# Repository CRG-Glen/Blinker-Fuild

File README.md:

# BLINKER FLUID

A completely pointless project.  

## What's this?  

Intended to sit inline with your 68000 CPU with LEDs on each signal that will light when that signal becomes active. 

It's just for fun and should not to be used for any diagnostic purposes, this isn't a logic probe!

There are 8nr 74HCT574s which are sampling each pin on the rising edge of a clock generated by a 555 timer.  
The 555 is running at a rate of approximately 50hz so will miss a lot of activity on the 68k.  There just
isn't enough room to do this with any accuracy but remember this is for fun only.  

You can adjust R71 and R72 to change the speed of the 555. 

## Assembly

Within the JLCPCB folder you will find Gerbers along with a BOM and CPL files suited to LCSC components.

The board can be produced with the HASL finish, no need to pay for EINT on this one but its mostly 0603 so 
get JLC (or equal) to do all SMD work.

Please note the BOM as included takes for RED LEDs for everything.  Feel free to change colours but remember 
you also need to adjust the resistor directly below each LED on the bottom side to suit your LEDs!

To keep the board tidy, there are no LED or Resistor designations on the PCB.  Just remember its all LEDs 
on the top side and all RESISTORs on the bottom side.  

## Bill of Materials

| Designation | Value | Type |
| --- | --- | --- |
| U1 - U8 | 74HCT574 | TSSOP20 |
| U9 | NE555 | TSSOP8 |
| LEDs | pick a colour | 0603 |
| Resistors | to suit your LED | 0603 |
| R71 | 1k ohm 1% | 0805 |
| R72 | 15kohm 1% | 0805 |
| C71 | 1uF | 0805 Tantalum |
| C72 | 10nF |0805 ceramic |
| C1-C8 + C73 | 0.1uF | 0603 ceramic |
| PINS | 0.5mm x 2.54mm x 9.7mm | individual machine pins |

## License

CERN Open Hardware Licence v2

Do with as you like just don't blame me if your computer, console or whatever else you install this in
goes up in smoke!

## Credits

PCB by CRG(Glen)

Artwork by Brick Studios

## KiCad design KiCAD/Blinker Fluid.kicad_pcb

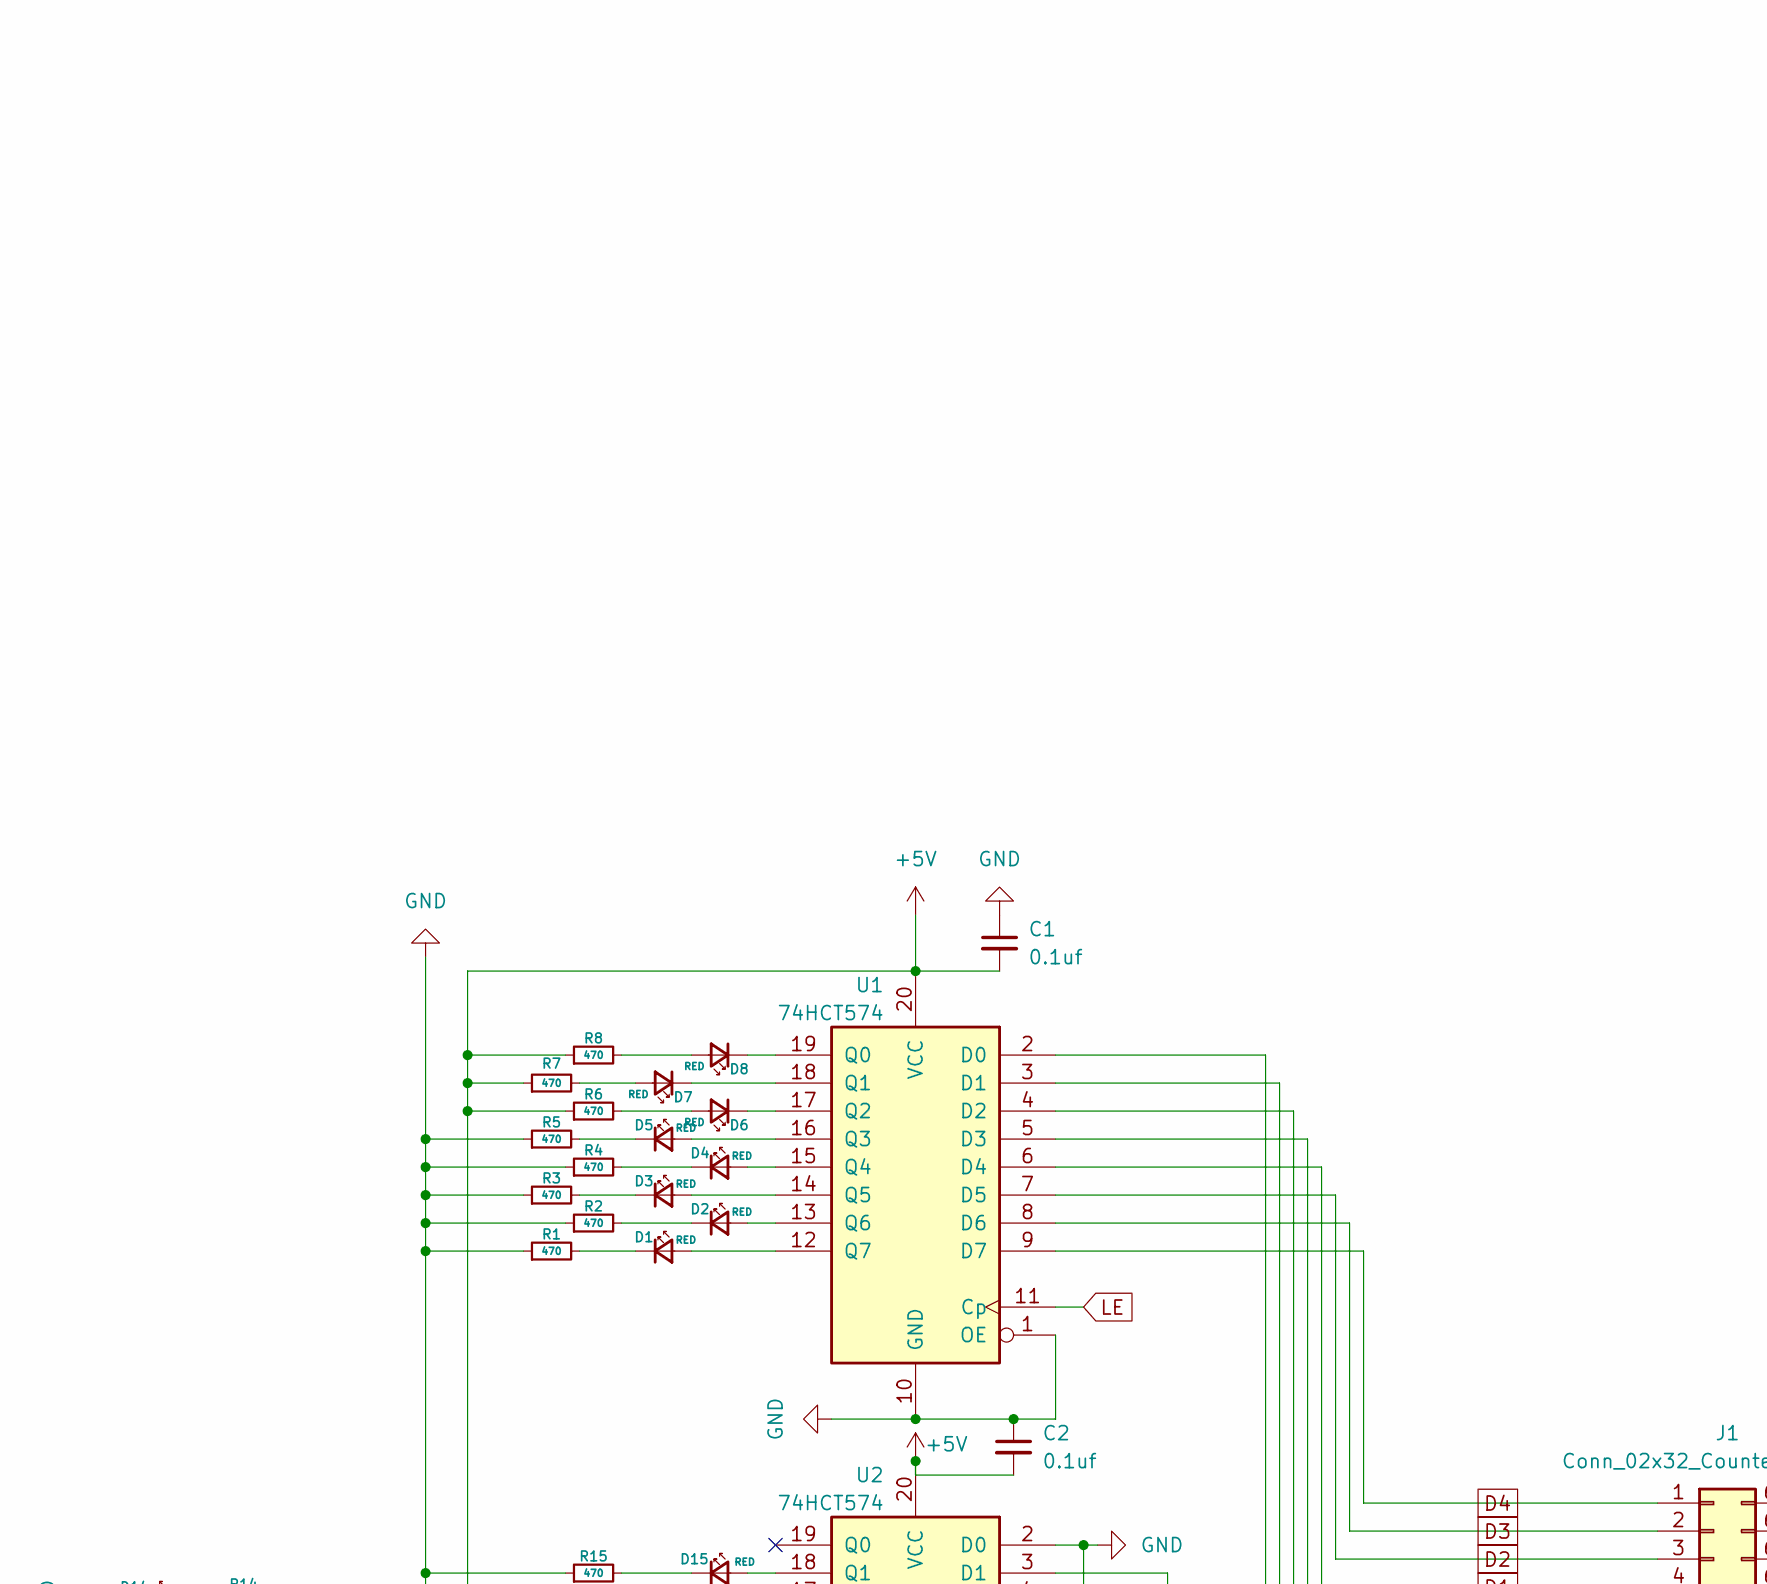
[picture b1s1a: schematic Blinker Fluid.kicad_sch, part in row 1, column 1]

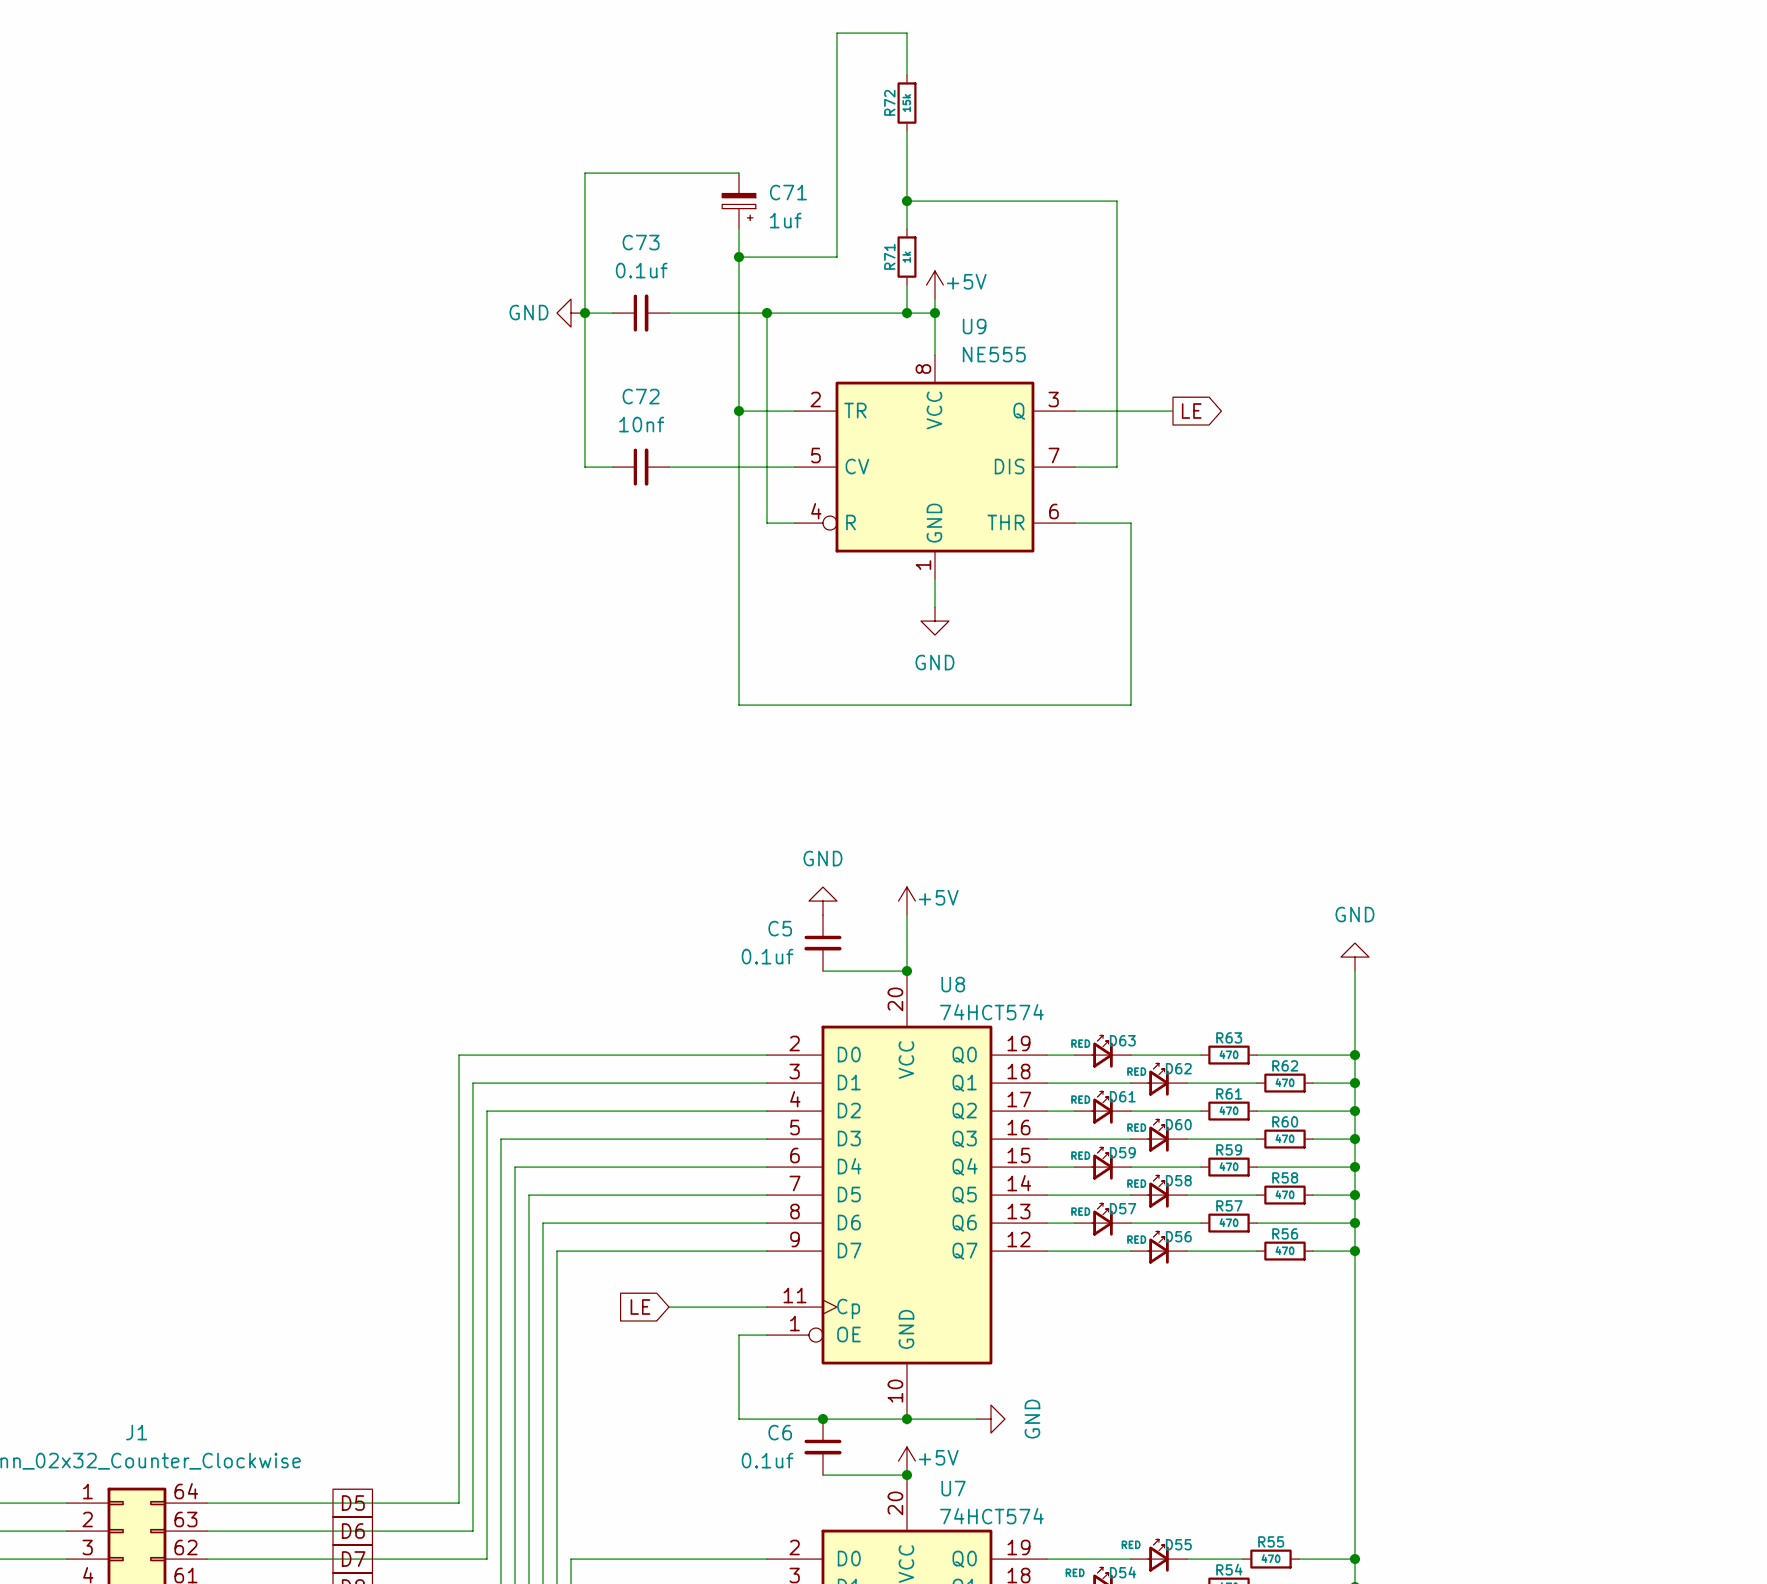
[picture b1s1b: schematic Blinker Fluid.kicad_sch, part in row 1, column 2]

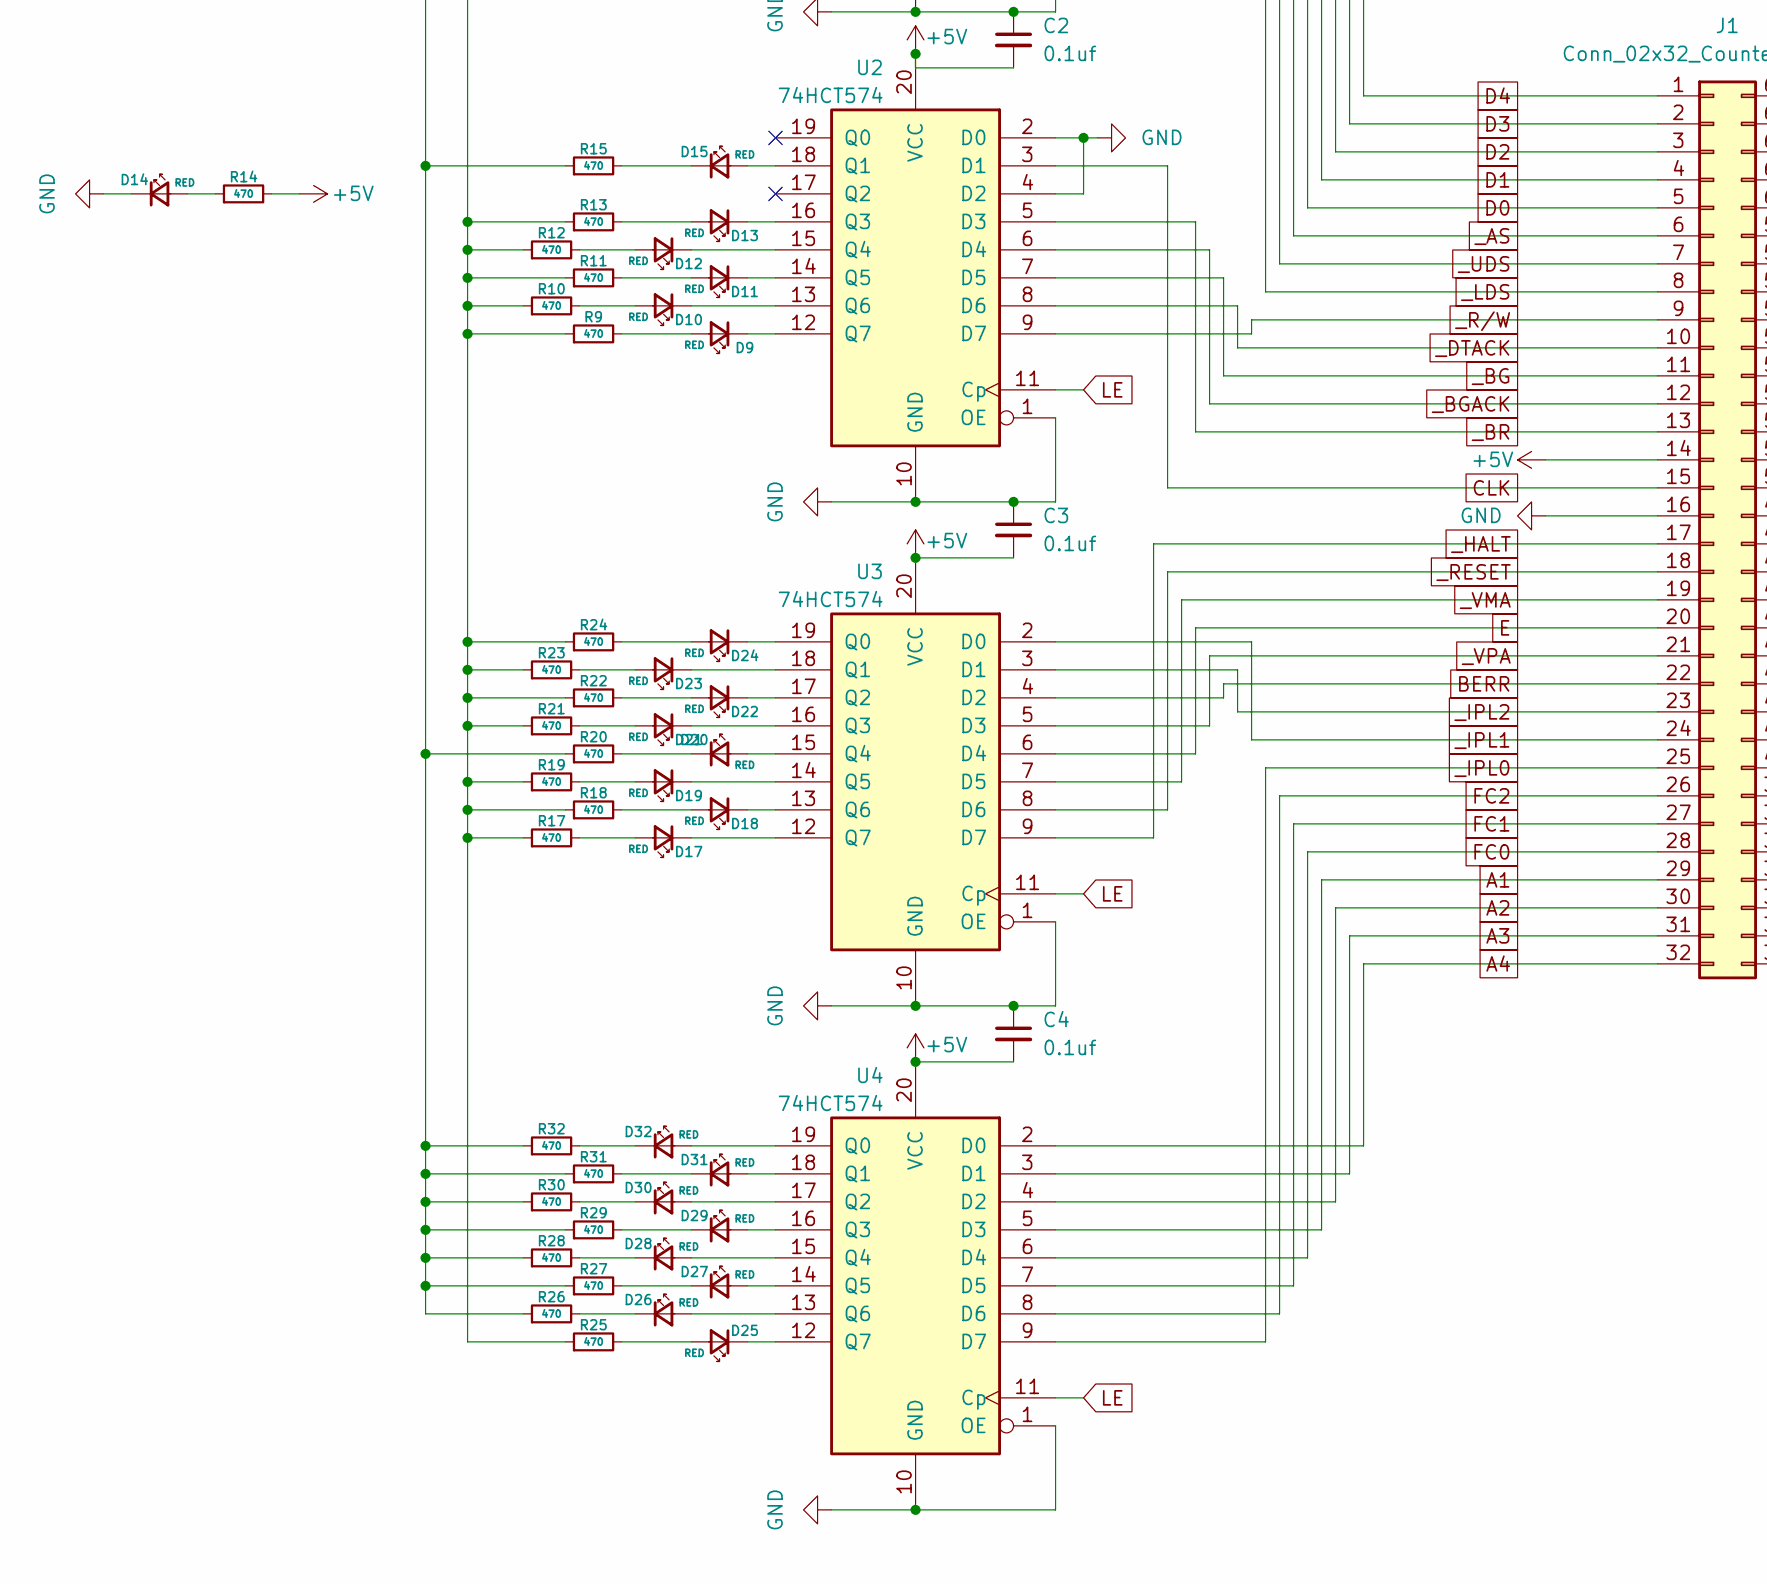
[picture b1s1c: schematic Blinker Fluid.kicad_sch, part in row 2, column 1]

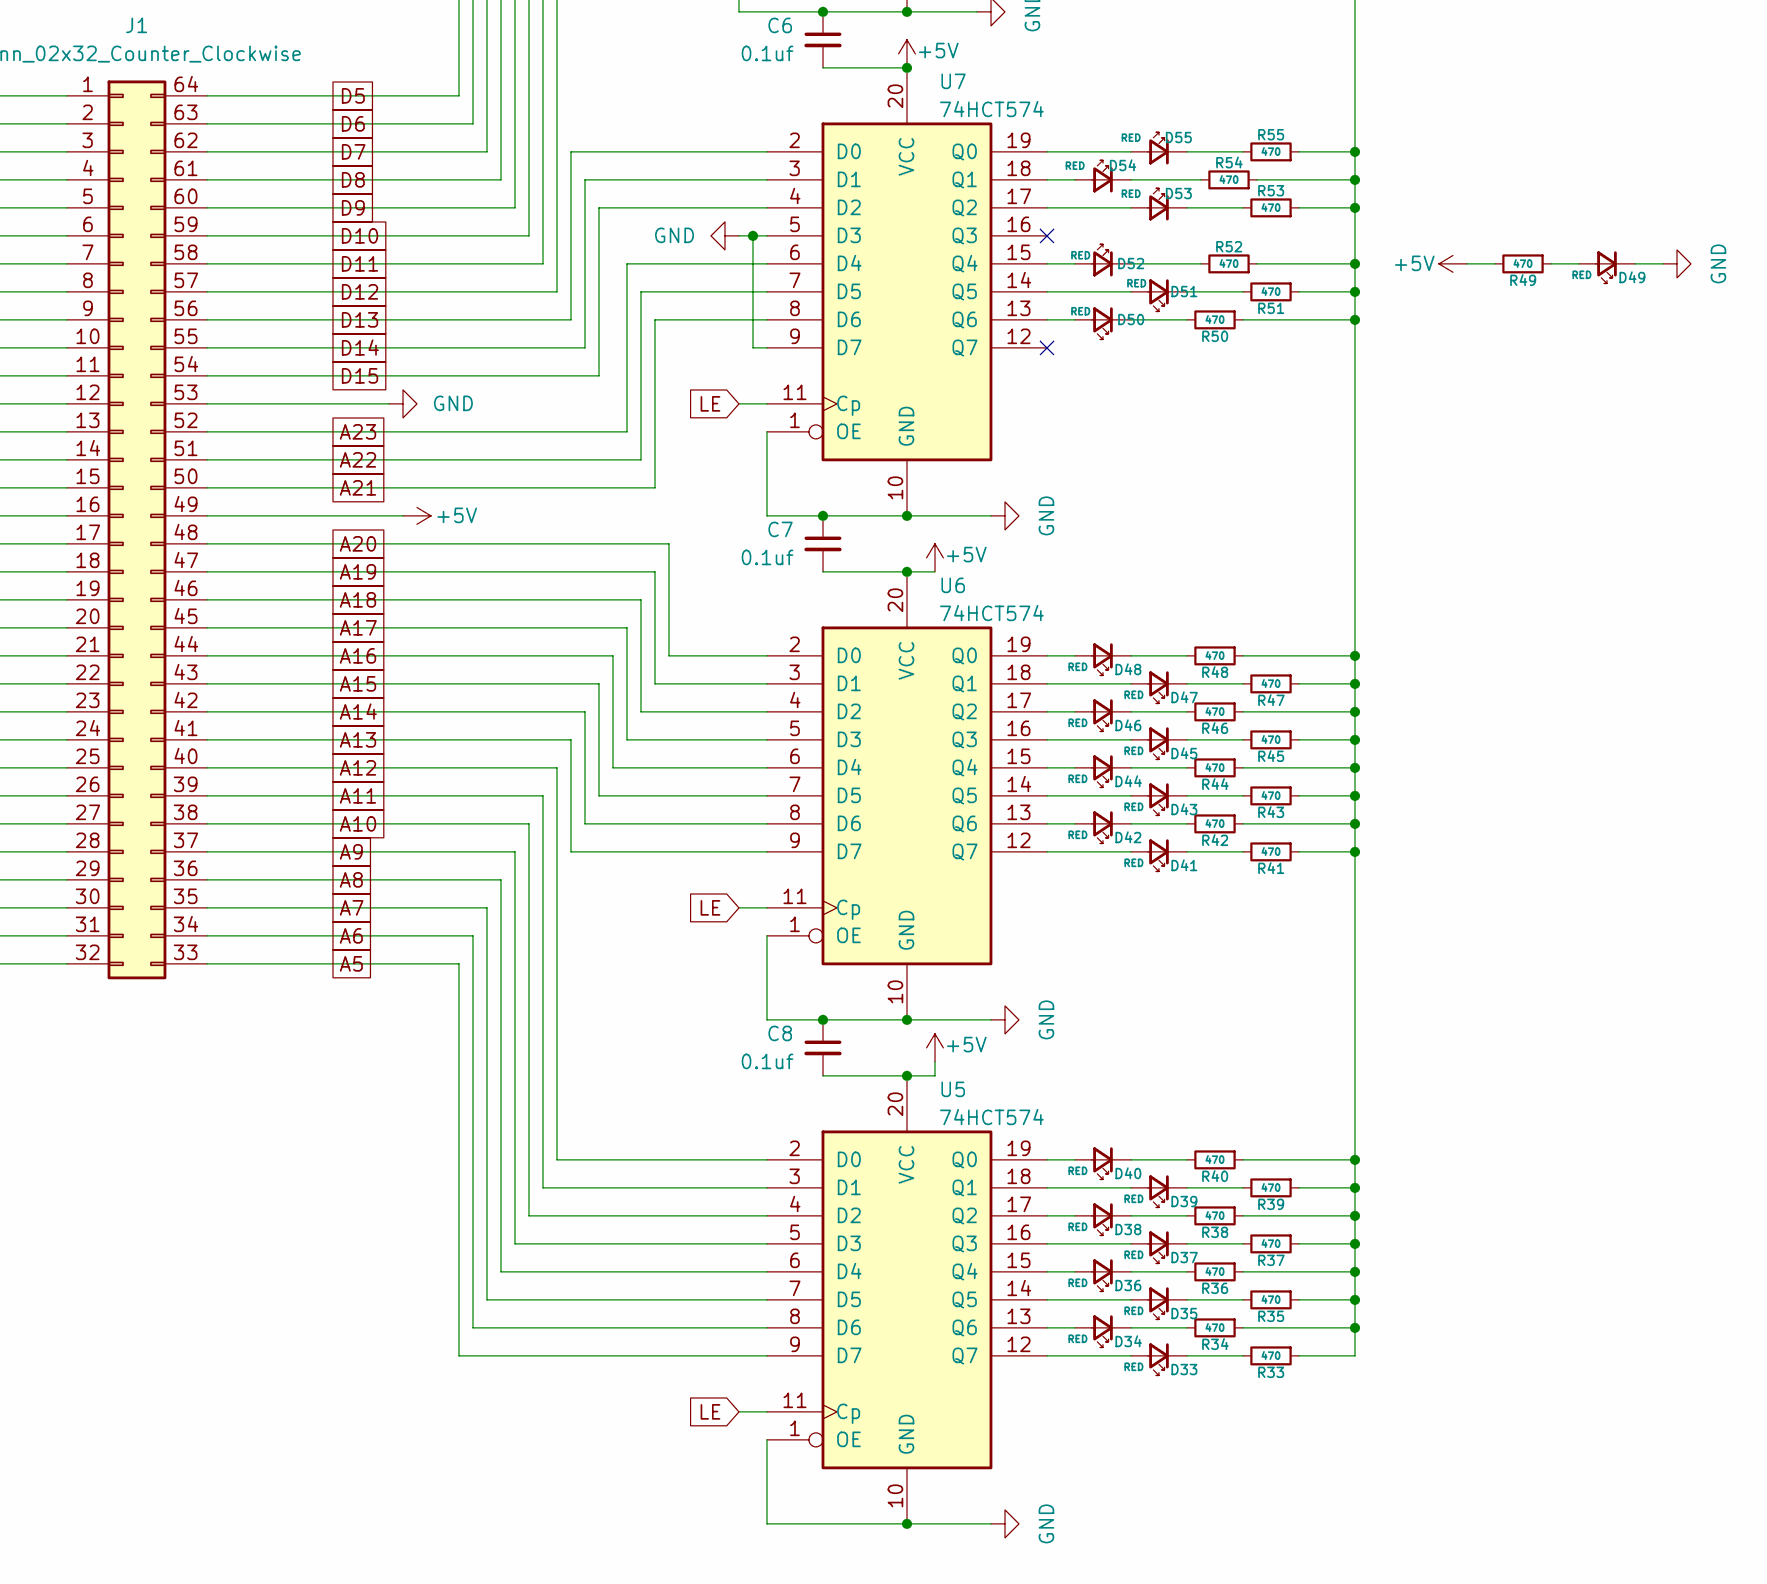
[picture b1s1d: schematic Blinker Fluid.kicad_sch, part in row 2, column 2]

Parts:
C1, C2, C3, C4, C5, C6, C7, C8, C73: 0.1uf; C_0603_1608Metric_Pad1.08x0.95mm_HandSolder; LCSC C14663
C71: 1uf; CP_EIA-2012-12_Kemet-R_Pad1.30x1.05mm_HandSolder; LCSC C7174
C72: 10nf; C_0805_2012Metric_Pad1.18x1.45mm_HandSolder; LCSC C15195
D1, D2, D3, D4, D5, D6, D7, D8, D9, D10, D11, D12, D13, D14, D15, D17, D18, D19, D20, D21, D22, D23, D24, D25, D26, D27, D28, D29, D30, D31, D32, D33, D34, D35, D36, D37, D38, D39, D40, D41, D42, D43, D44, D45, D46, D47, D48, D49, D50, D51, D52, D53, D54, D55, D56, D57, D58, D59, D60, D61, D62, D63: RED; LED_0603_1608Metric_Pad1.05x0.95mm_HandSolder; LCSC C2286
J1: Conn_02x32_Counter_Clockwise; DIP-64_W22.86mm_LongPads; LCSC C130723
R1, R2, R3, R4, R5, R6, R7, R8, R9, R10, R11, R12, R13, R14, R15, R17, R18, R19, R20, R21, R22, R23, R24, R25, R26, R27, R28, R29, R30, R31, R32, R33, R34, R35, R36, R37, R38, R39, R40, R41, R42, R43, R44, R45, R46, R47, R48, R49, R50, R51, R52, R53, R54, R55, R56, R57, R58, R59, R60, R61, R62, R63: 470; R_0603_1608Metric_Pad0.98x0.95mm_HandSolder; LCSC C23179
R71: 1k; R_0805_2012Metric_Pad1.20x1.40mm_HandSolder; LCSC C17513
R72: 15k; R_0805_2012Metric_Pad1.20x1.40mm_HandSolder; LCSC C17475
U1, U2, U3, U4, U5, U6, U7, U8: 74HCT574; TSSOP-20_4.4x6.5mm_P0.65mm; LCSC C2677898
U9: NE555; TSSOP-8_4.4x3mm_P0.65mm; LCSC C105643

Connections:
+5V: C1.2, C2.2, C3.2, C4.2, C5.2, C6.2, C7.2, C8.2, C73.2, J1.14, J1.49, R6.1, R7.1, R8.1, R9.1, R10.1, R11.1, R12.1, R13.1, R14.2, R17.1, R18.1, R19.1, R21.1, R22.1, R23.1, R24.1, R25.1, R49.2, R71.2, U1.20 (VCC), U2.20 (VCC), U3.20 (VCC), U4.20 (VCC), U5.20 (VCC), U6.20 (VCC), U7.20 (VCC), U8.20 (VCC), U9.4 (R), U9.8 (VCC)
A1: J1.29, U4.5 (D3)
A2: J1.30, U4.4 (D2)
A3: J1.31, U4.3 (D1)
A4: J1.32, U4.2 (D0)
A5: J1.33, U5.9 (D7)
A6: J1.34, U5.8 (D6)
A7: J1.35, U5.7 (D5)
A8: J1.36, U5.6 (D4)
A9: J1.37, U5.5 (D3)
A10: J1.38, U5.4 (D2)
A11: J1.39, U5.3 (D1)
A12: J1.40, U5.2 (D0)
A13: J1.41, U6.9 (D7)
A14: J1.42, U6.8 (D6)
A15: J1.43, U6.7 (D5)
A16: J1.44, U6.6 (D4)
A17: J1.45, U6.5 (D3)
A18: J1.46, U6.4 (D2)
A19: J1.47, U6.3 (D1)
A20: J1.48, U6.2 (D0)
A21: J1.50, U7.8 (D6)
A22: J1.51, U7.7 (D5)
A23: J1.52, U7.6 (D4)
BERR: J1.22, U3.4 (D2)
CLK: J1.15, U2.3 (D1)
D0: J1.5, U1.5 (D3)
D1: J1.4, U1.6 (D4)
D2: J1.3, U1.7 (D5)
D3: J1.2, U1.8 (D6)
D4: J1.1, U1.9 (D7)
D5: J1.64, U8.2 (D0)
D6: J1.63, U8.3 (D1)
D7: J1.62, U8.4 (D2)
D8: J1.61, U8.5 (D3)
D9: J1.60, U8.6 (D4)
D10: J1.59, U8.7 (D5)
D11: J1.58, U8.8 (D6)
D12: J1.57, U8.9 (D7)
D13: J1.56, U7.2 (D0)
D14: J1.55, U7.3 (D1)
D15: J1.54, U7.4 (D2)
E: J1.20, U3.6 (D4)
FC0: J1.28, U4.6 (D4)
FC1: J1.27, U4.7 (D5)
FC2: J1.26, U4.8 (D6)
GND: C1.1, C2.1, C3.1, C4.1, C5.1, C6.1, C7.1, C8.1, C71.2, C72.1, C73.1, D14.1 (K), D49.1 (K), J1.16, J1.53, R1.1, R2.1, R3.1, R4.1, R5.1, R15.1, R20.1, R26.1, R27.1, R28.1, R29.1, R30.1, R31.1, R32.1, R33.1, R34.1, R35.1, R36.1, R37.1, R38.1, R39.1, R40.1, R41.1, R42.1, R43.1, R44.1, R45.1, R46.1, R47.1, R48.1, R50.1, R51.1, R52.1, R53.1, R54.1, R55.1, R56.1, R57.1, R58.1, R59.1, R60.1, R61.1, R62.1, R63.1, U1.1 (OE), U1.10 (GND), U2.1 (OE), U2.2 (D0), U2.4 (D2), U2.10 (GND), U3.1 (OE), U3.10 (GND), U4.1 (OE), U4.10 (GND), U5.1 (OE), U5.10 (GND), U6.1 (OE), U6.10 (GND), U7.1 (OE), U7.5 (D3), U7.9 (D7), U7.10 (GND), U8.1 (OE), U8.10 (GND), U9.1 (GND)
LE: U1.11 (Cp), U2.11 (Cp), U3.11 (Cp), U4.11 (Cp), U5.11 (Cp), U6.11 (Cp), U7.11 (Cp), U8.11 (Cp), U9.3 (Q)
unnamed: D1.2 (A), U1.12 (Q7)
unnamed: D1.1 (K), R1.2
unnamed: D2.2 (A), U1.13 (Q6)
unnamed: D2.1 (K), R2.2
unnamed: D3.2 (A), U1.14 (Q5)
unnamed: D3.1 (K), R3.2
unnamed: D4.2 (A), U1.15 (Q4)
unnamed: D4.1 (K), R4.2
unnamed: D5.2 (A), U1.16 (Q3)
unnamed: D5.1 (K), R5.2
unnamed: D6.2 (A), R6.2
unnamed: D6.1 (K), U1.17 (Q2)
unnamed: D7.2 (A), R7.2
unnamed: D7.1 (K), U1.18 (Q1)
unnamed: D8.2 (A), R8.2
unnamed: D8.1 (K), U1.19 (Q0)
unnamed: D9.2 (A), R9.2
unnamed: D9.1 (K), U2.12 (Q7)
unnamed: D10.2 (A), R10.2
unnamed: D10.1 (K), U2.13 (Q6)
unnamed: D11.2 (A), R11.2
unnamed: D11.1 (K), U2.14 (Q5)
unnamed: D12.2 (A), R12.2
unnamed: D12.1 (K), U2.15 (Q4)
unnamed: D13.2 (A), R13.2
unnamed: D13.1 (K), U2.16 (Q3)
unnamed: D14.2 (A), R14.1
unnamed: D15.2 (A), U2.18 (Q1)
unnamed: D15.1 (K), R15.2
unnamed: D17.2 (A), R17.2
unnamed: D17.1 (K), U3.12 (Q7)
unnamed: D18.2 (A), R18.2
unnamed: D18.1 (K), U3.13 (Q6)
unnamed: D19.2 (A), R19.2
unnamed: D19.1 (K), U3.14 (Q5)
unnamed: D20.2 (A), U3.15 (Q4)
unnamed: D20.1 (K), R20.2
unnamed: D21.2 (A), R21.2
unnamed: D21.1 (K), U3.16 (Q3)
unnamed: D22.2 (A), R22.2
unnamed: D22.1 (K), U3.17 (Q2)
unnamed: D23.2 (A), R23.2
unnamed: D23.1 (K), U3.18 (Q1)
unnamed: D24.2 (A), R24.2
unnamed: D24.1 (K), U3.19 (Q0)
unnamed: D25.2 (A), R25.2
unnamed: D25.1 (K), U4.12 (Q7)
unnamed: D26.2 (A), U4.13 (Q6)
unnamed: D26.1 (K), R26.2
unnamed: D27.2 (A), U4.14 (Q5)
unnamed: D27.1 (K), R27.2
unnamed: D28.2 (A), U4.15 (Q4)
unnamed: D28.1 (K), R28.2
unnamed: D29.2 (A), U4.16 (Q3)
unnamed: D29.1 (K), R29.2
unnamed: D30.2 (A), U4.17 (Q2)
unnamed: D30.1 (K), R30.2
unnamed: D31.2 (A), U4.18 (Q1)
unnamed: D31.1 (K), R31.2
unnamed: D32.2 (A), U4.19 (Q0)
unnamed: D32.1 (K), R32.2
unnamed: D33.2 (A), U5.12 (Q7)
unnamed: D33.1 (K), R33.2
unnamed: D34.2 (A), U5.13 (Q6)
unnamed: D34.1 (K), R34.2
unnamed: D35.2 (A), U5.14 (Q5)
unnamed: D35.1 (K), R35.2
unnamed: D36.2 (A), U5.15 (Q4)
unnamed: D36.1 (K), R36.2
unnamed: D37.2 (A), U5.16 (Q3)
unnamed: D37.1 (K), R37.2
unnamed: D38.2 (A), U5.17 (Q2)
unnamed: D38.1 (K), R38.2
unnamed: D39.2 (A), U5.18 (Q1)
unnamed: D39.1 (K), R39.2
unnamed: D40.2 (A), U5.19 (Q0)
unnamed: D40.1 (K), R40.2
unnamed: D41.2 (A), U6.12 (Q7)
unnamed: D41.1 (K), R41.2
unnamed: D42.2 (A), U6.13 (Q6)
unnamed: D42.1 (K), R42.2
unnamed: D43.2 (A), U6.14 (Q5)
unnamed: D43.1 (K), R43.2
unnamed: D44.2 (A), U6.15 (Q4)
unnamed: D44.1 (K), R44.2
unnamed: D45.2 (A), U6.16 (Q3)
unnamed: D45.1 (K), R45.2
unnamed: D46.2 (A), U6.17 (Q2)
unnamed: D46.1 (K), R46.2
unnamed: D47.2 (A), U6.18 (Q1)
unnamed: D47.1 (K), R47.2
unnamed: D48.2 (A), U6.19 (Q0)
unnamed: D48.1 (K), R48.2
unnamed: D49.2 (A), R49.1
unnamed: D50.2 (A), U7.13 (Q6)
unnamed: D50.1 (K), R50.2
unnamed: D51.2 (A), U7.14 (Q5)
unnamed: D51.1 (K), R51.2
unnamed: D52.2 (A), U7.15 (Q4)
unnamed: D52.1 (K), R52.2
unnamed: D53.2 (A), U7.17 (Q2)
unnamed: D53.1 (K), R53.2
unnamed: D54.2 (A), U7.18 (Q1)
unnamed: D54.1 (K), R54.2
unnamed: D55.2 (A), U7.19 (Q0)
unnamed: D55.1 (K), R55.2
unnamed: D56.2 (A), U8.12 (Q7)
unnamed: D56.1 (K), R56.2
unnamed: D57.2 (A), U8.13 (Q6)
unnamed: D57.1 (K), R57.2
unnamed: D58.2 (A), U8.14 (Q5)
unnamed: D58.1 (K), R58.2
unnamed: D59.2 (A), U8.15 (Q4)
unnamed: D59.1 (K), R59.2
unnamed: D60.2 (A), U8.16 (Q3)
unnamed: D60.1 (K), R60.2
unnamed: D61.2 (A), U8.17 (Q2)
unnamed: D61.1 (K), R61.2
unnamed: D62.2 (A), U8.18 (Q1)
unnamed: D62.1 (K), R62.2
unnamed: D63.2 (A), U8.19 (Q0)
unnamed: D63.1 (K), R63.2
unnamed: C72.2, U9.5 (CV)
unnamed: R71.1, R72.2, U9.7 (DIS)
unnamed: C71.1, R72.1, U9.2 (TR), U9.6 (THR)
_AS: J1.6, U1.4 (D2)
_BG: J1.11, U2.7 (D5)
_BGACK: J1.12, U2.6 (D4)
_BR: J1.13, U2.5 (D3)
_DTACK: J1.10, U2.8 (D6)
_HALT: J1.17, U3.9 (D7)
_IPL0: J1.25, U4.9 (D7)
_IPL1: J1.24, U3.2 (D0)
_IPL2: J1.23, U3.3 (D1)
_LDS: J1.8, U1.2 (D0)
_RESET: J1.18, U3.8 (D6)
_R/W: J1.9, U2.9 (D7)
_UDS: J1.7, U1.3 (D1)
_VMA: J1.19, U3.7 (D5)
_VPA: J1.21, U3.5 (D3)

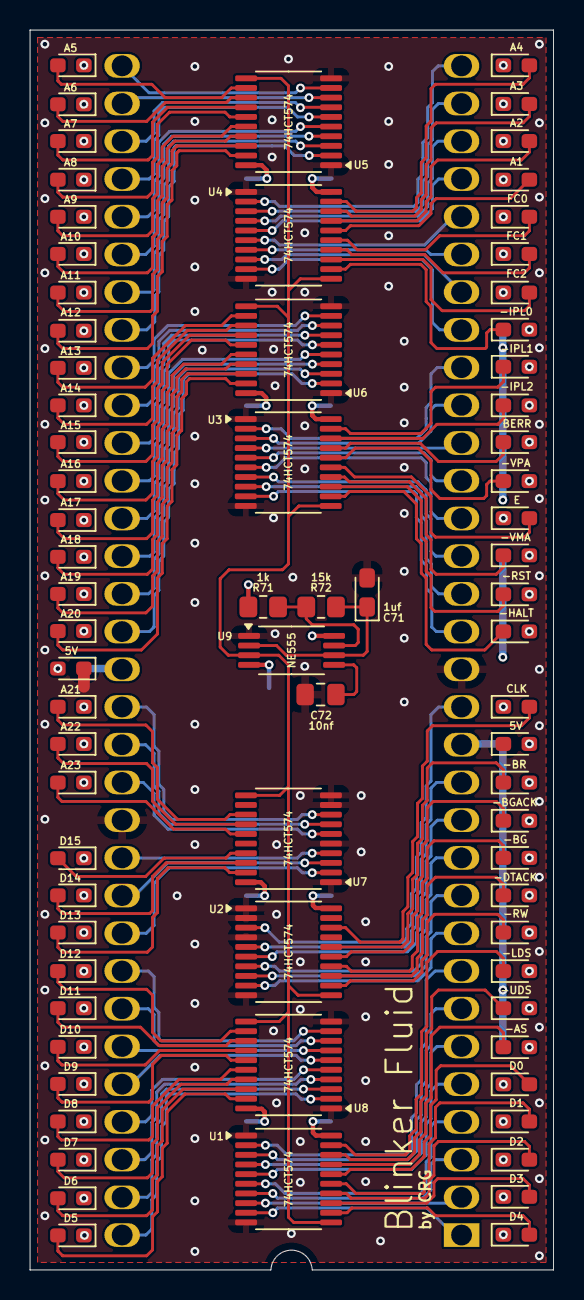
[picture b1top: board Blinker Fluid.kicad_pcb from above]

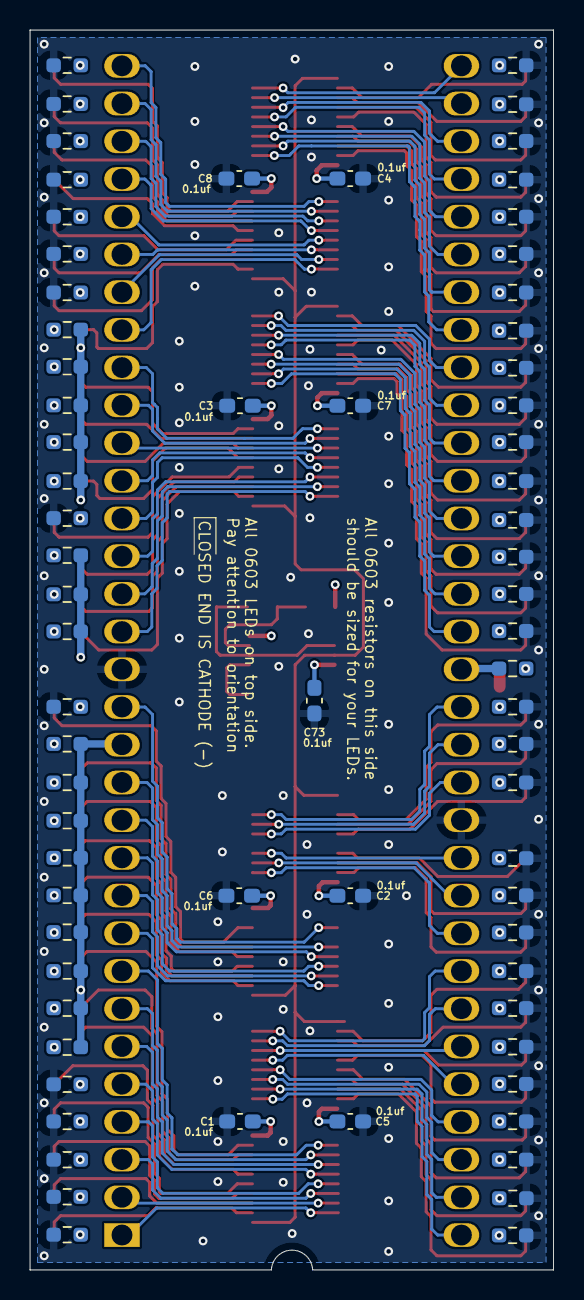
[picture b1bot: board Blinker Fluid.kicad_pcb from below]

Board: 4 copper layers, 35.2 x 83.5 mm, 147 parts (71 on the bottom side), 188 nets.

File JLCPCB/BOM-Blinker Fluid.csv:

Comment,Designator,Footprint,LCSC,Quantity
0.1uf,"C1,C2,C3,C4,C5,C6,C7,C73,C8",C_0603_1608Metric_Pad1.08x0.95mm_HandSolder,C14663,9
10nf,C72,C_0805_2012Metric_Pad1.18x1.45mm_HandSolder,C1710,1
15k,R72,R_0805_2012Metric_Pad1.20x1.40mm_HandSolder,C17475,1
1k,R71,R_0805_2012Metric_Pad1.20x1.40mm_HandSolder,C17513,1
1uf,C71,CP_EIA-2012-12_Kemet-R_Pad1.30x1.05mm_HandSolder,C7174,1
470,"R1,R10,R11,R12,R13,R14,R15,R17,R18,R19,R2,R20,R21,R22,R23,R24,R25,R26,R27,R28,R29,R3,R30,R31,R32,R33,R34,R35,R36,R37,R38,R39,R4,R40,R41,R42,R43,R44,R45,R46,R47,R48,R49,R5,R50,R51,R52,R53,R54,R55,R56,R57,R58,R59,R6,R60,R61,R62,R63,R7,R8,R9",R_0603_1608Metric_Pad0.98x0.95mm_HandSolder,C23179,62
74HCT574,"U1,U2,U3,U4,U5,U6,U7,U8",TSSOP-20_4.4x6.5mm_P0.65mm,C2677898,8
NE555,U9,TSSOP-8_4.4x3mm_P0.65mm,C105643,1
RED,"D1,D10,D11,D12,D13,D14,D15,D17,D18,D19,D2,D20,D21,D22,D23,D24,D25,D26,D27,D28,D29,D3,D30,D31,D32,D33,D34,D35,D36,D37,D38,D39,D4,D40,D41,D42,D43,D44,D45,D46,D47,D48,D49,D5,D50,D51,D52,D53,D54,D55,D56,D57,D58,D59,D6,D60,D61,D62,D63,D7,D8,D9",LED_0603_1608Metric_Pad1.05x0.95mm_HandSolder,C2286,62
Conn_02x32_Counter_Clockwise,J1,DIP-64_W22.86mm_LongPads,,1

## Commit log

2026-02-16 revised
2026-02-17 Updated 17-02-26
2026-02-17 README updated
2026-02-25 Updated 25-02-26
2026-03-20 Minor corrections
2026-03-20 Add artwork credit to README
2026-03-20 Update capacitor C72 description to '0805 ceramic'
2026-03-20 Picture updated
2026-03-20 Update credits to include contributor's name
2026-03-20 Update pin specifications in README
2026-04-23 Update project status in README
2026-04-24 PCB revised to clear short
